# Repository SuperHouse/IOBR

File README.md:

I/O Breakout Shield
===================
Copyright 2017-2019 SuperHouse Pty Ltd  
SuperHouse site:  <www.superhouse.tv>  

Breaks out sets of I/O pins to 2x6 pin headers.

Features:

 * 3 x 2x6 shrouded pin headers
 * Each header provides 8 x data lines, GND, VIN, IOREF, and RESET

More information is available at:

  http://www.superhouse.tv/iobr

INSTALLATION
------------
The design is saved as an EAGLE project. EAGLE PCB design software is
available from www.cadsoftusa.com free for non-commercial use. To use
this project download it and place the directory containing these files
into the "eagle" directory on your computer. Then open EAGLE and
navigate to the project.

DISTRIBUTION
------------
The specific terms of distribution of this project are governed by the
license referenced below.

LICENSE
-------
Licensed under the TAPR Open Hardware License (www.tapr.org/OHL).
The "license" folder within this repository also contains a copy of
this license in plain text format.

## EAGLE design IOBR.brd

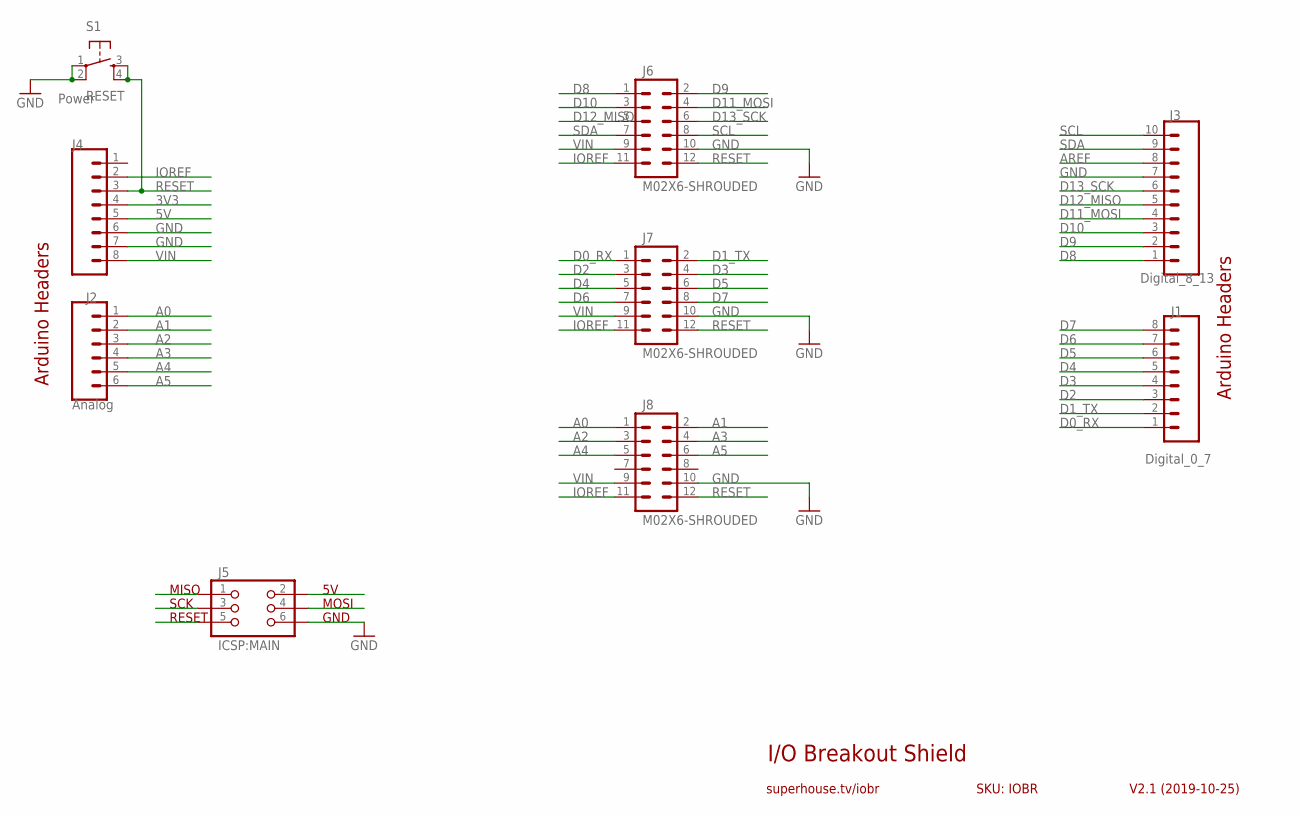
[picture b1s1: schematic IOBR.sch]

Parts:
J1: Digital_0_7; 1X08-P-BELOW
J2: Analog; 1X06-P-BELOW
J3: Digital_8_13; 1X10-P-BELOW
J4: Power; 1X08-P-BELOW
J5: ICSP:MAIN; 2X03-ICSP-ST-BELOW
J6, J7, J8: M02X6-SHROUDED; 2X06-SHROUDED
S1: RESET; TACTILE-PTH-6MM

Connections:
3V3: J4.4
5V: J4.5
A0: J2.1, J8.1
A1: J2.2, J8.2
A2: J2.3, J8.3
A3: J2.4, J8.4
A4: J2.5, J8.5
A5: J2.6, J8.6
AREF: J3.8
D0_RX: J1.1, J7.1
D1_TX: J1.2, J7.2
D2: J1.3, J7.3
D3: J1.4, J7.4
D4: J1.5, J7.5
D5: J1.6, J7.6
D6: J1.7, J7.7
D7: J1.8, J7.8
D8: J3.1, J6.1
D9: J3.2, J6.2
D10: J3.3, J6.3
D11_MOSI: J3.4, J6.4
D12_MISO: J3.5, J6.5
D13_SCK: J3.6, J6.6
GND: J3.7, J4.6, J4.7, J5.6, J6.10, J7.10, J8.10, S1.1, S1.2
IOREF: J4.2, J6.11, J7.11, J8.11
RESET: J4.3, J6.12, J7.12, J8.12, S1.3, S1.4
SCL: J3.10, J6.8
SDA: J3.9, J6.7
VIN: J4.8, J6.9, J7.9, J8.9

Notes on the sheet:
I/O Breakout Shield
V2.1 (2019-10-25)
superhouse.tv/iobr
SKU: IOBR
Arduino Headers
GND
MISO
RESET
SCK
MOSI

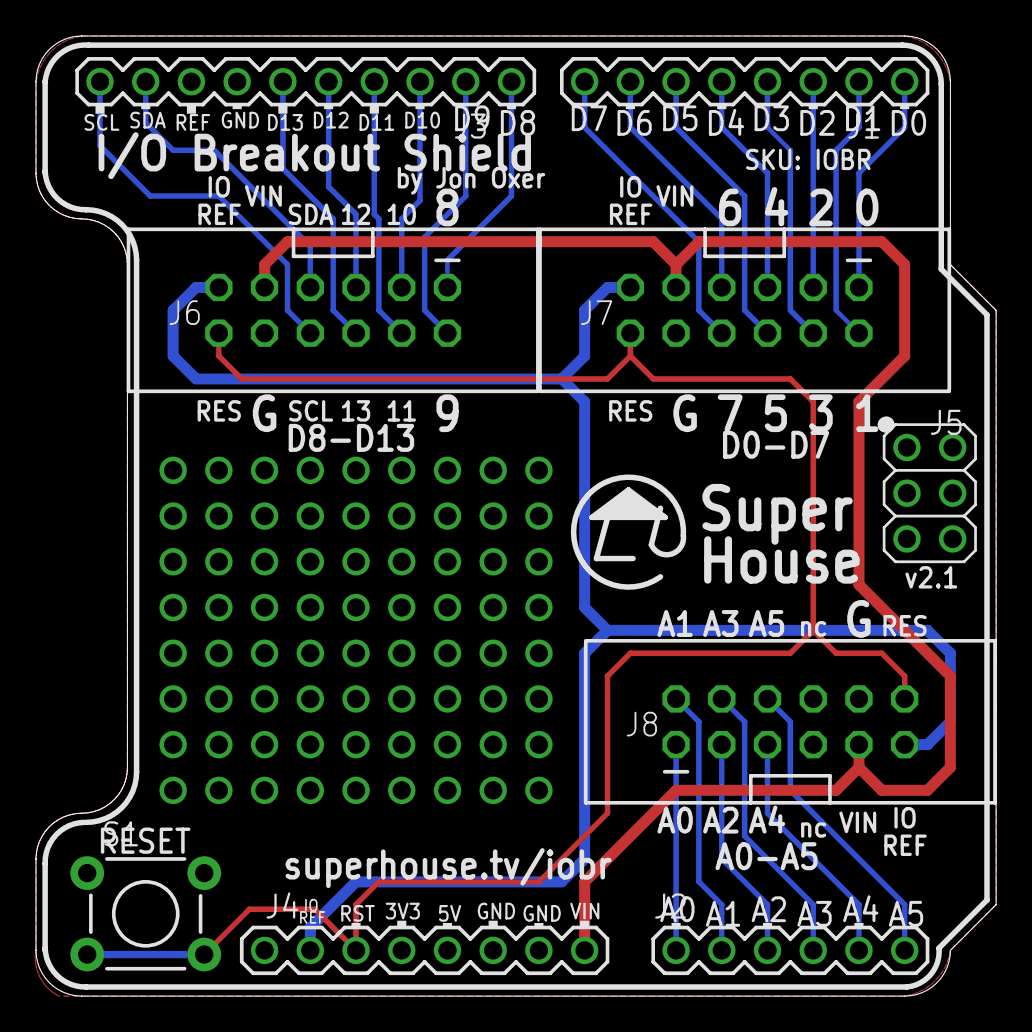
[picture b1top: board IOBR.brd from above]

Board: 2 copper layers, 53.3 x 53.3 mm, 9 parts (0 on the bottom side), 26 nets.

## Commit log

2017-07-21 Initial project import for possible v1.0 release
2017-07-24 Expanded headers to 2x6 to include IOREF and RESET for v2.0 release
2019-09-13 Converted parts to SuperHouse libraries
2019-10-25 Update for v2.1 release
2019-10-25 Added preview image
2020-03-17 Trivial silkscreen tweaks

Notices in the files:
IOBR.brd:
(C)2019 SuperHouse
